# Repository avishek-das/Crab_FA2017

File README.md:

# Crab_FA2017
Fab Academy 2017 final project of mine. A robot controlled from Grasshopper

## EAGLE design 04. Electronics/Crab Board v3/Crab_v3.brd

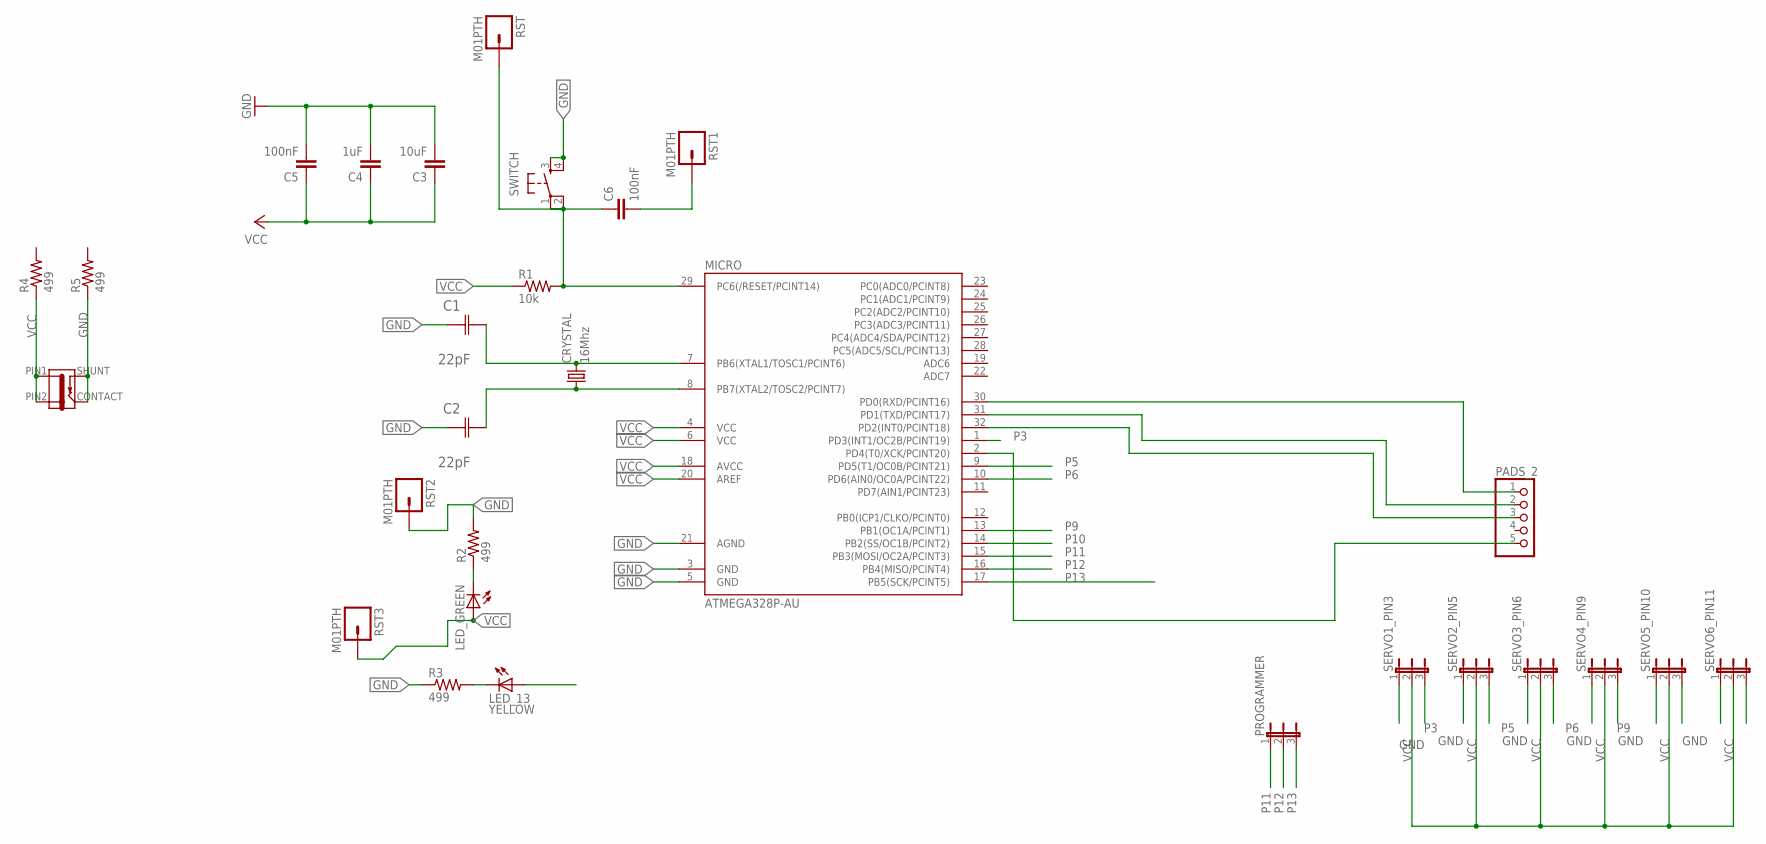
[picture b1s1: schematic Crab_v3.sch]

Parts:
C1, C2: 22pF; CAPC3216X178N
C3: 10uF; 1206
C4: 1uF; 1206
C5, C6: 100nF; 1206
CRYSTAL: 16Mhz; CSM-7X-DU
J1: JACK-2.1MM; PJ-002AH-SMT
LED_13: YELLOW; 1206
LED_GREEN: LED1206; 1206
MICRO: ATMEGA328P-AU; TQFP32-08
PADS_2: PINHD-1X5; 1X05
PROGRAMMER: JP2E; JP2
R1: 10k; 1206
R2, R3, R4, R5: 499; 1206
RST, RST1, RST2, RST3: M01PTH; 1X01
SERVO1_PIN3, SERVO2_PIN5, SERVO3_PIN6, SERVO4_PIN9, SERVO5_PIN10, SERVO6_PIN11: JP2E; JP2
SWITCH: 6MM_SWITCH6MM_SWITCH; 6MM_SWITCH

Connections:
GND: C1.1 (C1), C2.1 (C1), C3.2, C4.2, C5.2, J1.CONTACT, J1.SHUNT, MICRO.3 (GND), MICRO.5 (GND), MICRO.21 (AGND), R2.2, R3.1, R5.1, RST2.1, SERVO1_PIN3.1, SERVO2_PIN5.1, SERVO3_PIN6.1, SERVO4_PIN9.1, SERVO5_PIN10.1, SERVO6_PIN11.1, SWITCH.3 (S), SWITCH.4 (S1)
unnamed: C1.2 (C2), CRYSTAL.2, MICRO.7 (PB6(XTAL1/TOSC1/PCINT6))
unnamed: C6.2, RST1.1
unnamed: MICRO.30 (PD0(RXD/PCINT16)), PADS_2.1
unnamed: C2.2 (C2), CRYSTAL.1, MICRO.8 (PB7(XTAL2/TOSC2/PCINT7))
unnamed: MICRO.31 (PD1(TXD/PCINT17)), PADS_2.2
unnamed: MICRO.32 (PD2(INT0/PCINT18)), PADS_2.3
unnamed: MICRO.2 (PD4(T0/XCK/PCINT20)), PADS_2.5
unnamed: LED_GREEN.2 (C), R2.1
unnamed: LED_13.2 (C), R3.2
unnamed: C6.1, MICRO.29 (PC6(/RESET/PCINT14)), R1.2, RST.1, SWITCH.1, SWITCH.2 (P1)
P3: LED_13.1 (A), MICRO.1 (PD3(INT1/OC2B/PCINT19)), SERVO1_PIN3.3
P5: MICRO.9 (PD5(T1/OC0B/PCINT21)), SERVO2_PIN5.3
P6: MICRO.10 (PD6(AIN0/OC0A/PCINT22)), SERVO3_PIN6.3
P9: MICRO.13 (PB1(OC1A/PCINT1)), SERVO4_PIN9.3
P10: MICRO.14 (PB2(SS/OC1B/PCINT2)), SERVO5_PIN10.3
P11: MICRO.15 (PB3(MOSI/OC2A/PCINT3)), PROGRAMMER.1, SERVO6_PIN11.3
P12: MICRO.16 (PB4(MISO/PCINT4)), PROGRAMMER.2
P13: MICRO.17 (PB5(SCK/PCINT5)), PROGRAMMER.3
VCC: C3.1, C4.1, C5.1, J1.PIN1, J1.PIN2, LED_GREEN.1 (A), MICRO.4 (VCC), MICRO.6 (VCC), MICRO.18 (AVCC), MICRO.20 (AREF), R1.1, R4.1, RST3.1, SERVO1_PIN3.2, SERVO2_PIN5.2, SERVO3_PIN6.2, SERVO4_PIN9.2, SERVO5_PIN10.2, SERVO6_PIN11.2

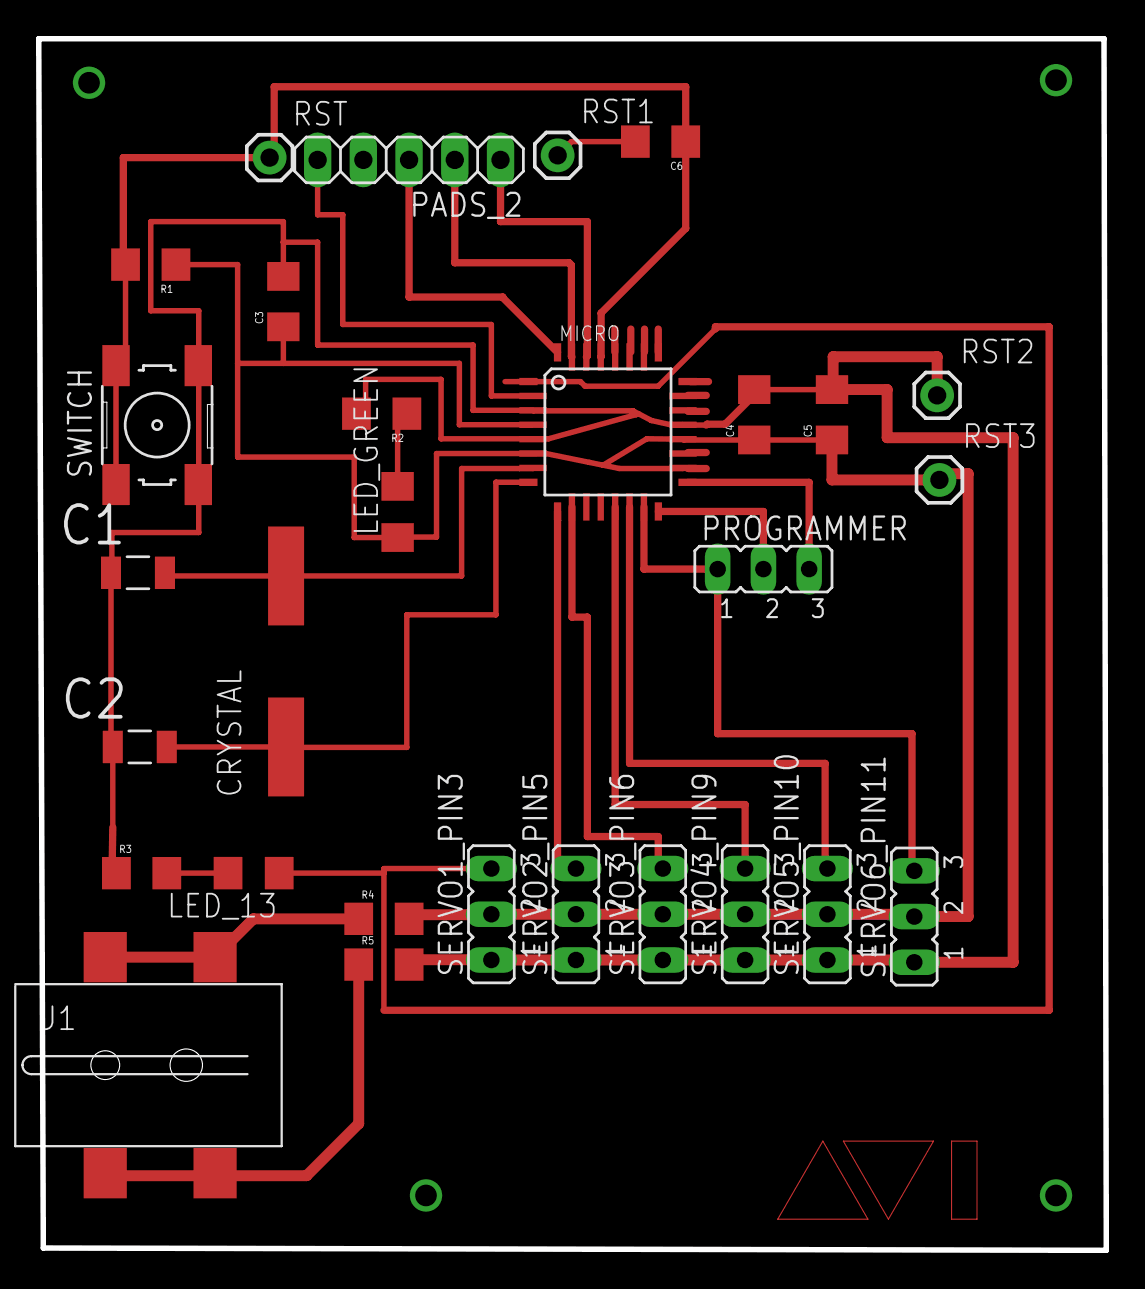
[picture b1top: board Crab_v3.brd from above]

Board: 2 copper layers, 59.3 x 67.3 mm, 29 parts (0 on the bottom side), 20 nets.

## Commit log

2017-06-06 first repo
2017-06-07 0706
2017-06-08 0906
2017-06-08 gh added
2017-06-10 1006
2017-06-10 1006-2
2017-06-11 1106
2017-06-12 1206
2017-06-13 1306
2017-06-14 1506
2017-06-16 1606
2017-06-16 1706
2017-06-17 1806

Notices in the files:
parts and their libraries:
01_SparkFun: Licensing: CC v3.0 Share-Alike You are welcome to use this library for commercial purposes.
